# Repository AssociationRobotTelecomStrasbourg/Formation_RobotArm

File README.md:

# Formation RTS - édition confinée
## Arduino base + Bras-robot

### Inscription Tinkercad

Tout d'abord, rendez-vous sur le site : [Tinkercad](https://www.tinkercad.com/)

Deux choix s'offrent à vous pour la suite (le choix reste votre): 
- Créer un compte
- Utilisation sans s'inscrire  

Vous ferez de toute façon parti d'une classe où tout ce que vous ferez sera enregistré et pourra être récupé par RTS si besoin.

#### 1- Créer un compte
  - [ ] Cliquez sur "Rejoindre maintenant" en haut à droite de la page
  - [ ] "Créer un compte personnel" puis "S'inscrire avec une adresse électronique"
  - [ ] Suivez simplement la procédure
  - [ ] Aller sur votre "dashboard" (il suffit une fois conencter de cliquer sur le logo en haut à gauche de la page)
  - [ ] Puis cliquez dans la colonne de gauche sur "Rejoindre la classe" (écrit en vert)
  - [ ] Rentrez tout simplement le code "TC2G-1TSS-55M3"

#### 2- Utilisation sans s'inscrire
  - [ ] Cliquez sur "Rejoindre maintenant" en haut à droite de la page
  - [ ] "Etudiants, rejoignez un cours"
  - [ ] Le code de la salle est le suivant "TC2G-1TSS-55M3"
  - [ ] Cliquez sur "Rejoindre avec le surnom"
  - [ ] Rentrer le surnom qu'un membre RTS vous donnera au moment de la formation
  - [ ] Vous avez maintenant accès à un espace personnel, pas de crainte, tout ce que vous ferez s'enregistrera automatiquement tant que vous faites parti de la classe.

### Créer un circuit

  1. Aller sur votre "dashboard" (il suffit une fois conencter de cliquer sur le logo en haut à gauche de la page)
  2. Dans la colonne de droite, cliquez sur "Circuits" puis créer un circuit.
  3. Pour ajouter un élément sur votre circuit, il suffit de le sélectionner pour pouvoir le placer ensuite. Pour le faire tourner, appuyez sur la touche "R".
  4. Pour relier les éléments de votre circuit entre eux, cliquez sur la pin à relier, un fil apparait, reliez le à l'autre pin.

### Simuler votre circuit
  
  1. Cliquez sur "Code" en haut à droite de votre fenêtre. Dans le menu déroulant sélectionnez "Texte". Vous devriez voir apparaître la structure type d'un code en Arduino.
  2. En bas de la fenêtre qui vient de s'afficher, vous avez accès également accès au "Moniteur Série".
  3. Une fois votre code écrit : cliquez sur "Démarrer la simulation" à côté de "Code".
  4. Si votre code contient une erreur, le logiciel vous le fera savoir. Si tout va bien, vous pouvez déjà visualiser sur le circuit ou le moniteur série la simulation.

### Resources et fichiers d'aide
  
Vous pourrez retrouver certains montages et codes sur mon profil Tinkercad (un peu vide pour le moment)  
Pour celà, dans votre "dashboard" cliquez tout en haut à droite à côté de votre logo de profil sur la loupe. Tapez "Robot Télécom Strasbourg", sélectionnez l'onglet "Personnes" et cliquez sur le profil qui s'affiche. Sous l'onglet "Circuits" vous pourrez avoir acccès aux montages. 

Malheureusement, il n'y a pas d'encodeur sur Tinkercad, pour simuler de quoi bouger votre curseur sur un écran, vous pouvez utiliser des boutons ou un potentiomètre. Pour ce qui est de l'écran LCD i2C, il n'y a pas de module i2c disponible, tous les branchements seront à faire à la main (pas de problème ! Le montage est déjà disponible si vous fouillez un peu dans les menus déroulants). Le code d'initialisation ne sera pas tout à fait le même non plus car nous ne pouvons pas utiliser la librairie "Wire.h", mais vous pouvez vous baser sur celui du montage déjà disponible.

# Amusez-vous !

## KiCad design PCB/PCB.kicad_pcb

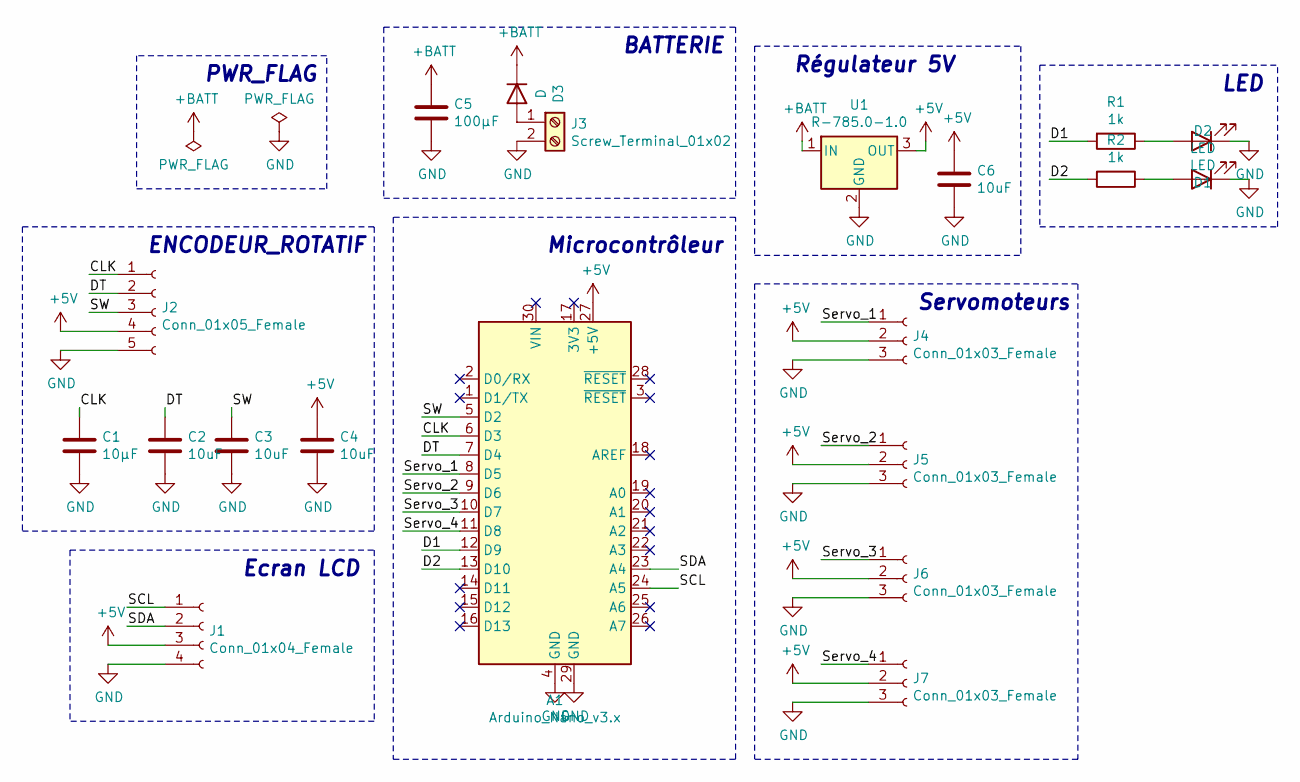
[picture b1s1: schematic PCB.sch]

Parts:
A1: Arduino_Nano_v3.x; Arduino_Nano
C1: 10µF; C_1206_3216Metric_Pad1.42x1.75mm_HandSolder
C2, C3, C4, C6: 10uF; C_1206_3216Metric_Pad1.42x1.75mm_HandSolder
C5: 100µF; CP_Elec_6.3x7.7
D1, D2: LED; LED_D5.0mm
D3: D; D_SMA_Handsoldering
J1: Conn_01x04_Female; PinHeader_1x04_P2.54mm_Vertical
J2: Conn_01x05_Female; PinHeader_1x05_P2.54mm_Vertical
J3: Screw_Terminal_01x02; TerminalBlock_bornier-2_P5.08mm
J4, J5, J6, J7: Conn_01x03_Female; PinHeader_1x03_P2.54mm_Vertical
R1, R2: 1k; R_1206_3216Metric_Pad1.42x1.75mm_HandSolder
U1: R-785.0-1.0; Converter_DCDC_RECOM_R-78E-0.5_THT

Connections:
+5V: A1.27 (+5V), C4.1, C6.1, J1.3, J2.4, J4.2, J5.2, J6.2, J7.2, U1.3 (OUT)
+BATT: C5.1, D3.1 (K), U1.1 (IN)
/CLK: A1.6 (D3), C1.1, J2.1
/D1: A1.12 (D9), R1.2
/D2: A1.13 (D10), R2.2
/DT: A1.7 (D4), C2.1, J2.2
/SCL: A1.24 (A5), J1.1
/SDA: A1.23 (A4), J1.2
/SW: A1.5 (D2), C3.1, J2.3
/Servo_1: A1.8 (D5), J4.1
/Servo_2: A1.9 (D6), J5.1
/Servo_3: A1.10 (D7), J6.1
/Servo_4: A1.11 (D8), J7.1
GND: A1.4 (GND), A1.29 (GND), C1.2, C2.2, C3.2, C4.2, C5.2, C6.2, D1.1 (K), D2.1 (K), J1.4, J2.5, J3.2, J4.3, J5.3, J6.3, J7.3, U1.2 (GND)
unnamed: D1.2 (A), R1.1
unnamed: D2.2 (A), R2.1
unnamed: D3.2 (A), J3.1

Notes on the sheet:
Microcontrôleur
Régulateur 5V
Ecran LCD
Servomoteurs
ENCODEUR_ROTATIF
PWR_FLAG
BATTERIE
LED

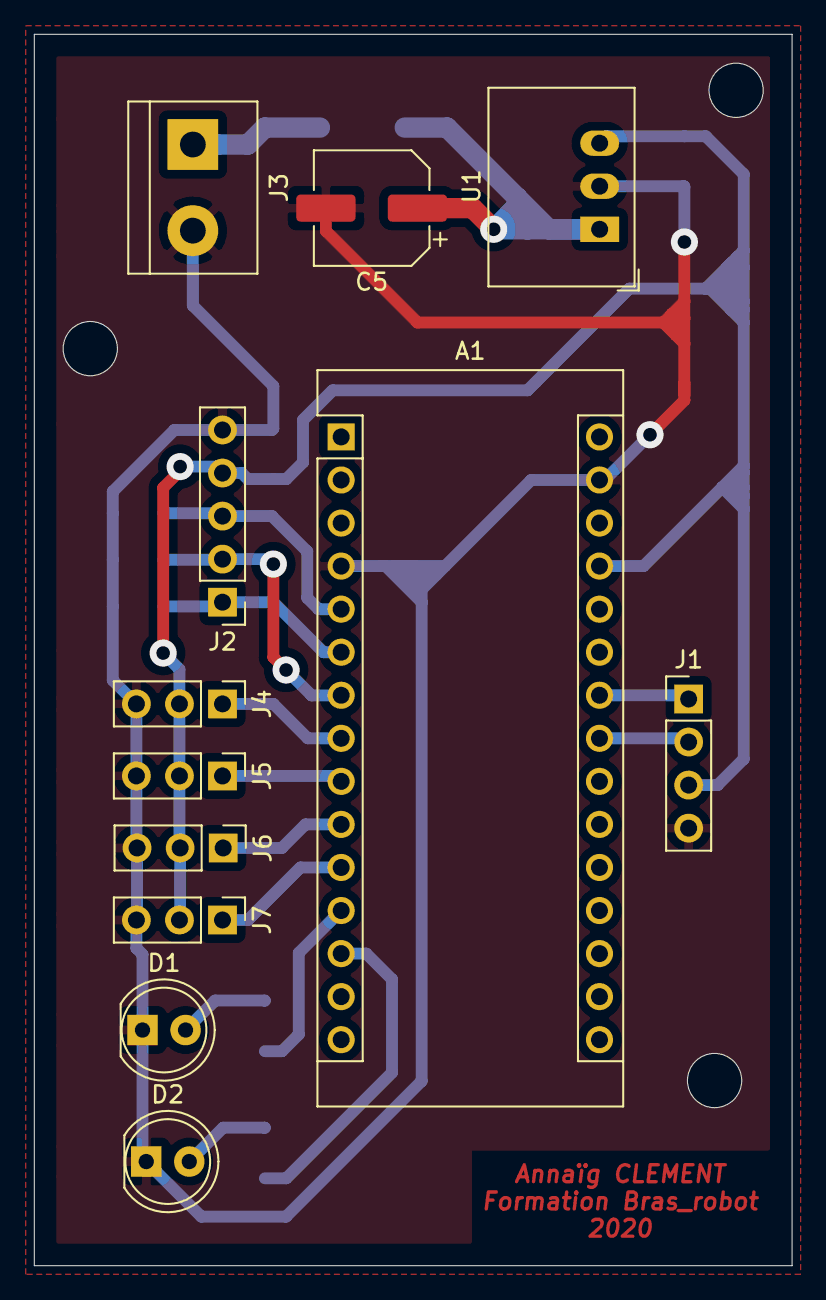
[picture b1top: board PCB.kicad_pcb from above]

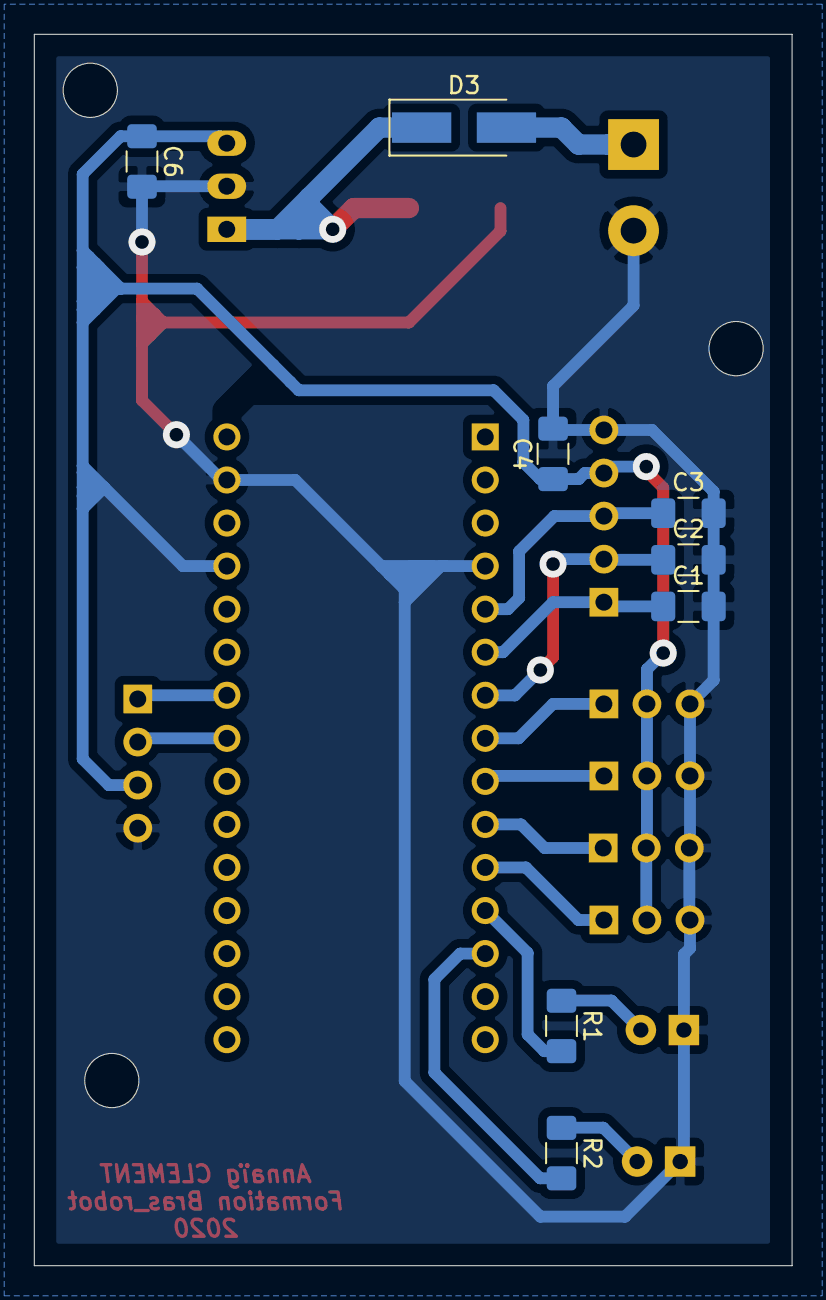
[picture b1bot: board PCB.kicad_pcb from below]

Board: 2 copper layers, 44.7 x 72.6 mm, 20 parts (8 on the bottom side), 17 nets.

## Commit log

2020-07-17 Ajout des fichiers de CAO électronique
2020-07-18 MAJ : Mounting holes
2020-10-11 Add files via upload
    Ajout code arduino
2020-10-11 Add files via upload
    MàJ
2020-11-07 Rename README.md to Tinkercad_tuto.md
2020-11-07 Rename Tinkercad_tuto.md to README.md
